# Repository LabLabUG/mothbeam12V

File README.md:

# mothbeam12V
A version of the MothBeam optimized for 12V operation. Select the LEDs according to your needs and according to the part numbers shown in the schematics. It is designed for a
IMS substrate PCB.

This project is CERN-OHL-W-2.0 open source hardware. It is has now officially been certified as open source hardware by the Open Source Hardware Association with UUID DE000156.

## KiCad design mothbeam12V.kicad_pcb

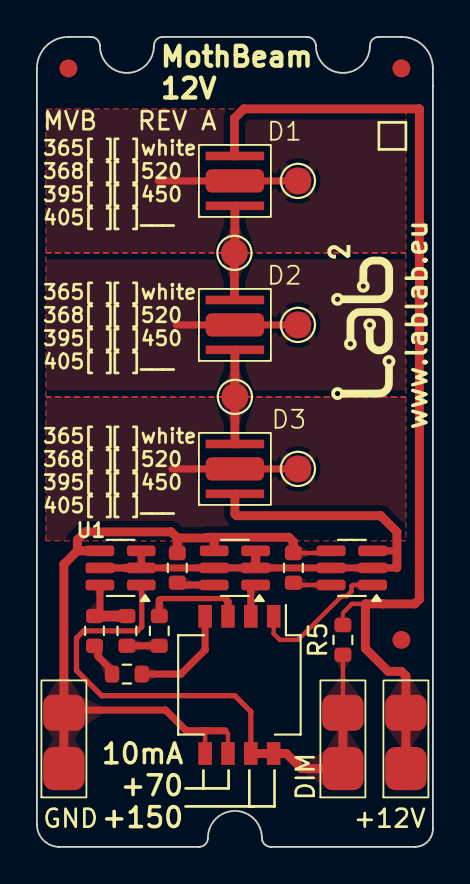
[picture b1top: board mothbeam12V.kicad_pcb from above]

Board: 2 copper layers, 22.0 x 45.0 mm, 26 parts (0 on the bottom side), 18 nets.

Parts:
D1: LED1; Wuerth_HP_Ceramic
D2: LED2; Wuerth_HP_Ceramic
D3: LED3; Wuerth_HP_Ceramic
FID1, FID2, FID3: Fiducial; Fiducial_1mm_Mask3mm
H1: LabLab Logo; logo_10mm_5mm
J1: +VDC; 2834171-3
J3: EN; 2834171-3
J8: GND; 2834171-3
R1, R2, R3, R4, R5, R6, R9: 5.1 1/3 W; R_0603_1608Metric
SW2: SW_DIP_x04; SW_DIP_SPSTx04_Slide_KingTek_DSHP04TS_W7.62mm_P1.27mm
TP1, TP2, TP3, TP4, TP5: LED2+; TestPoint_Pad_D1.5mm
U1, U2, U3: BCR421U; SC-74-6_1.55x2.9mm_P0.95mm

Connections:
/LED+: D1.2 (A), J1.1, R5.1
/LED-: D3.1 (K), U1.2 (OUT), U1.3 (OUT), U1.5 (OUT), U2.2 (OUT), U2.3 (OUT), U2.5 (OUT), U3.2 (OUT), U3.3 (OUT), U3.5 (OUT)
/T1: D1.3 (PAD), TP2.1
/T2: D2.3 (PAD), TP4.1
/T3: D3.3 (PAD), TP5.1
EN: J3.1, R5.2, SW2.7, SW2.8, U1.1 (EN)
GND: J8.1, R1.2, R9.2, SW2.5, SW2.6, U1.4 (GND), U2.4 (GND), U3.4 (GND)
unnamed: D1.1 (K), D2.2 (A), TP3.1
unnamed: D2.1 (K), D3.2 (A), TP1.1
unnamed: R2.2, R6.1
unnamed: R3.2, R4.1
unnamed: R4.2, SW2.4
unnamed: R6.2, SW2.3
unnamed: R2.1, R3.1, U1.6 (REXT)
unnamed: SW2.2, U2.1 (EN)
unnamed: R9.1, U2.6 (REXT)
unnamed: SW2.1, U3.1 (EN)
unnamed: R1.1, U3.6 (REXT)

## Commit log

2025-07-01 added CERN Open Hardware Licence Version 2 - Weakly Reciprocal
2025-07-02 added OSHWA license, pdf and schematics
